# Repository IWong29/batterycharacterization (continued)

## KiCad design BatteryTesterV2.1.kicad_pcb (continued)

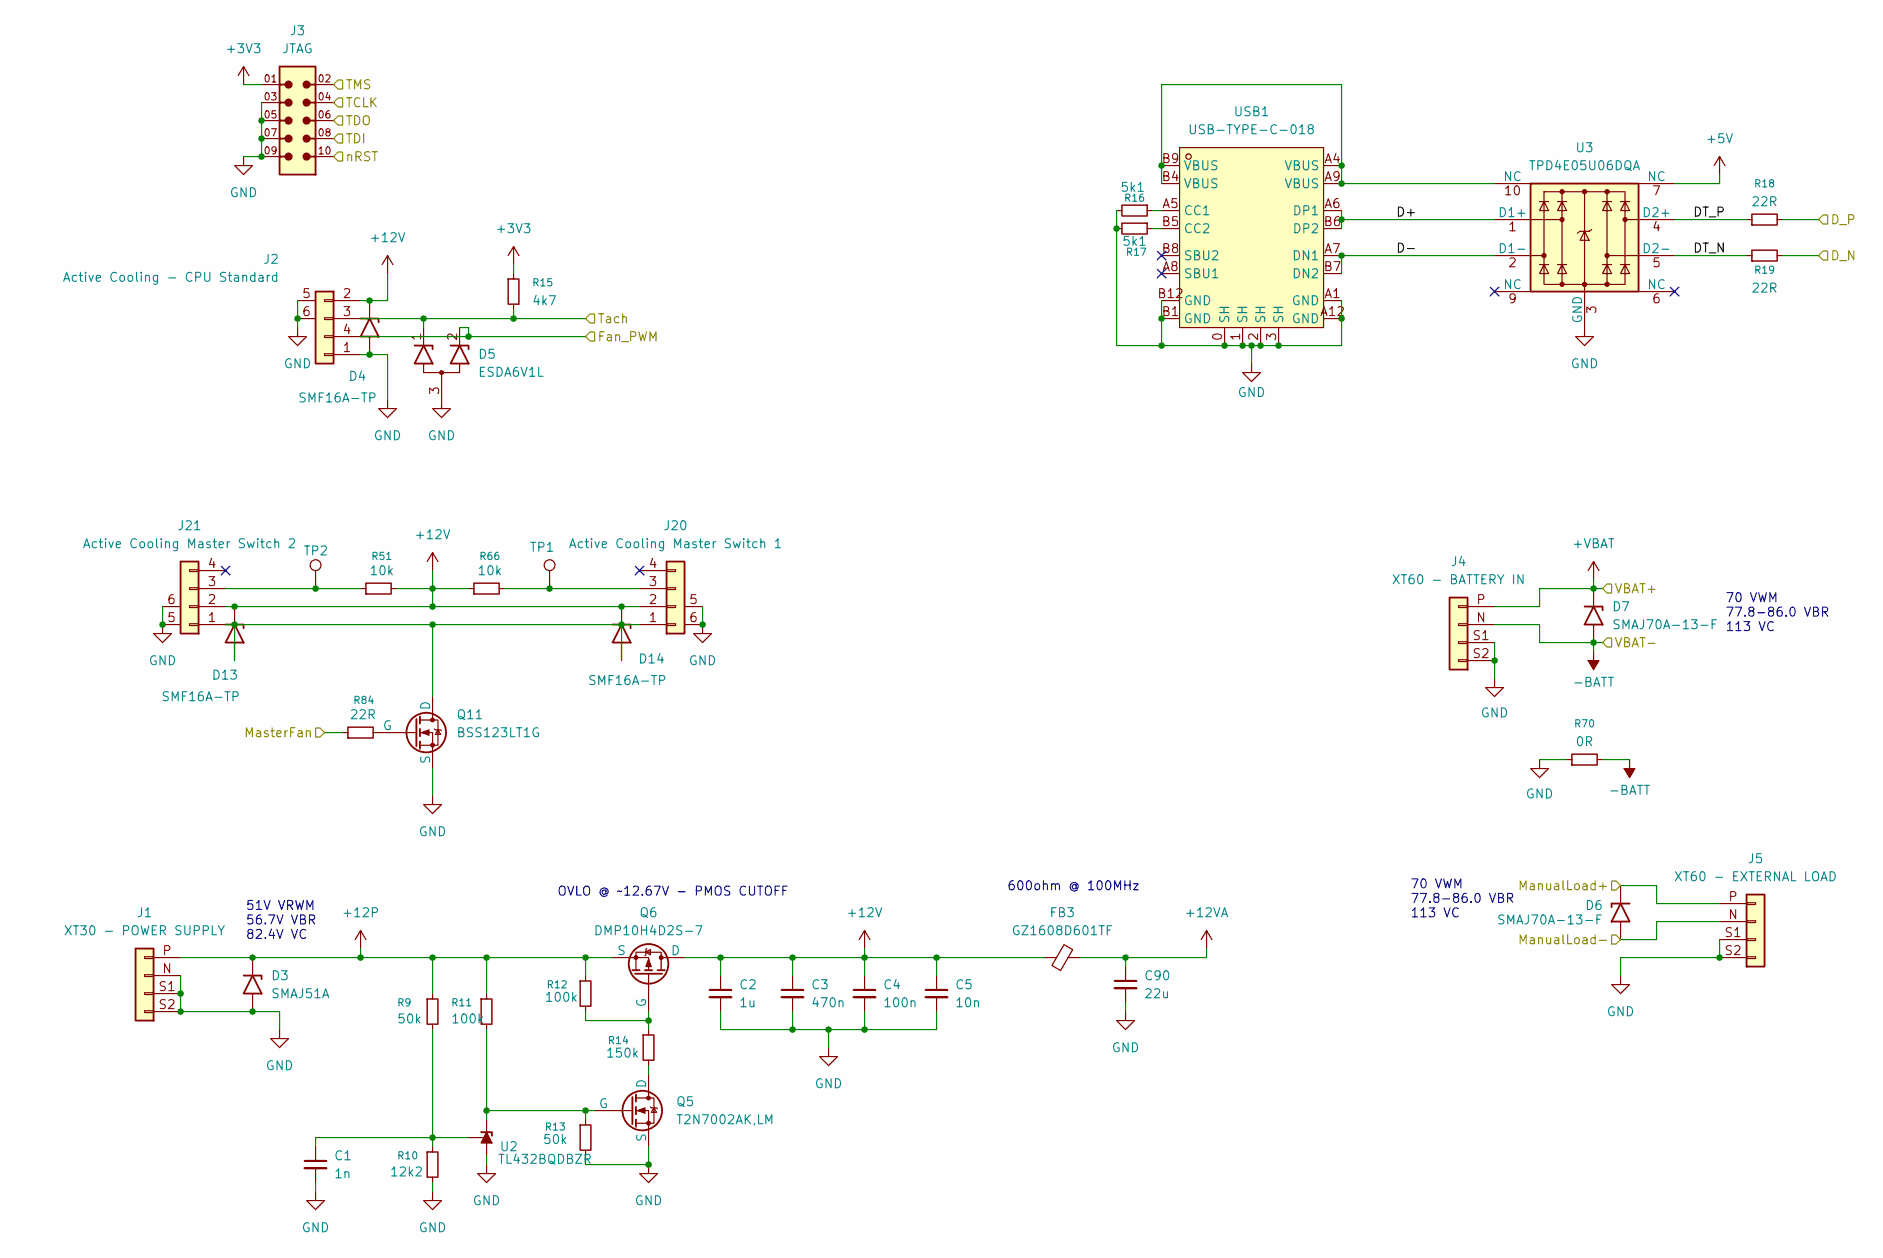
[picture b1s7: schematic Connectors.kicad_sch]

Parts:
C1: 1n; C_0603_1608Metric
C2: 1u; C_0603_1608Metric
C3: 470n; C_0603_1608Metric
C4: 100n; C_0603_1608Metric
C5: 10n; C_0603_1608Metric
C90: 22u; C_1206_3216Metric
D3: SMAJ51A; D_SMA
D4, D13, D14: SMF16A-TP; D_SMF
D5: ESDA6V1L; SOT-23
D6, D7: SMAJ70A-13-F; D_SMA
FB3: GZ1608D601TF; C_0603_1608Metric
J1: XT30 - POWER SUPPLY; AMASS_XT30PW-M
J2: Active Cooling - CPU Standard; CONN-SMD_4P-P1.00_SM04B-SRSS-TB-LF-SN
J3: JTAG; JTAG_SAMTEC_FTSH-105-01-X-DV-P-K-X
J4: XT60 - BATTERY IN; XT60
J5: XT60 - EXTERNAL LOAD; XT60
J20: Active Cooling Master Switch 1; CONN-SMD_4P-P1.00_SM04B-SRSS-TB-LF-SN
J21: Active Cooling Master Switch 2; CONN-SMD_4P-P1.00_SM04B-SRSS-TB-LF-SN
Q5: T2N7002AK,LM; SOT-23-3
Q6: DMP10H4D2S-7; SOT-23-3
Q11: BSS123LT1G; SOT-23-3
R9, R13: 50k; C_0805_2012Metric
R10: 12k2; R_0603_1608Metric
R11, R12: 100k; R_0603_1608Metric
R14: 150k; R_0603_1608Metric
R15: 4k7; R_0603_1608Metric
R16, R17: 5k1; R_0603_1608Metric
R18, R19: 22R; R_0603_1608Metric
R51, R66: 10k; C_0805_2012Metric
R70: 0R; R_0603_1608Metric
R84: 22R; C_0805_2012Metric
TP1, TP2: TestPoint; TestPoint_Pad_D1.0mm
U2: TL432BQDBZR; SOT-23-3
U3: TPD4E05U06DQA; USON-10_2.5x1.0mm_P0.5mm
USB1: USB-TYPE-C-018; USB-C_SMD-TYPE-C18; MPN USB-TYPE-C-018; LCSC Part C2927038

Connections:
+3V3: J3.01, R15.1; also elsewhere on the board
+5V: U3.7 (NC); also elsewhere on the board
+12P: D3.1 (A1), J1.P (Pin_4), Q6.3 (S), R9.1, R11.1, R12.1; also elsewhere on the board
+12V: C2.1, C3.1, C4.1, C5.1, D4.1 (A1), D13.1 (A1), D14.1 (A1), FB3.1, J2.2, J20.2, J21.2, Q6.1 (D), R51.2, R66.1; also elsewhere on the board
+12VA: C90.1, FB3.2; also elsewhere on the board
+VBAT: D7.1 (A1), J4.P (Pin_4); also elsewhere on the board
-BATT: D6.2 (A2), D7.2 (A2), J4.N (Pin_3), J5.N (Pin_3), R70.2; also elsewhere on the board
/BatteryV2/ExternalLoad+: D6.1 (A1), J5.P (Pin_4); also elsewhere on the board
/Connectors/D+: U3.1 (D1+), USB1.A6 (DP1), USB1.B6 (DP2)
/Connectors/D-: U3.2 (D1-), USB1.A7 (DN1), USB1.B7 (DN2)
/Connectors/DT_N: R19.1, U3.5 (D2-)
/Connectors/DT_P: R18.1, U3.4 (D2+)
/Connectors/D_N: R19.2; also elsewhere on the board
/Connectors/D_P: R18.2; also elsewhere on the board
/Connectors/Fan_PWM: D5.2 (K2), J2.4; also elsewhere on the board
/Connectors/MasterFan: R84.1; also elsewhere on the board
/Connectors/TCLK: J3.04; also elsewhere on the board
/Connectors/TDI: J3.08; also elsewhere on the board
/Connectors/TDO: J3.06; also elsewhere on the board
/Connectors/TMS: J3.02; also elsewhere on the board
/Connectors/Tach: D5.1 (K1), J2.3, R15.2; also elsewhere on the board
/Connectors/nRST: J3.10; also elsewhere on the board
GND: C1.2, C2.2, C3.2, C4.2, C5.2, C90.2, D3.2 (A2), D4.2 (A2), D5.3 (A), J1.N (Pin_3), J1.S1 (Pin_2), J1.S2 (Pin_1), J2.1, J2.5, J2.6, J3.03, J3.05, J3.07, J3.09, J4.S1 (Pin_2), J4.S2 (Pin_1), J5.S1 (Pin_2), J5.S2 (Pin_1), J20.5, J20.6, J21.5, J21.6, Q5.3 (S), Q11.3 (S), R10.2, R13.2, R16.2, R17.2, R70.1, U2.3 (A), U3.3 (GND), U3.8 (GND), USB1.0 (SH), USB1.1 (SH), USB1.2 (SH), USB1.3 (SH), USB1.A1 (GND), USB1.A12 (GND), USB1.B1 (GND), USB1.B12 (GND); also elsewhere on the board
unnamed: D13.2 (A2), D14.2 (A2), J20.1, J21.1, Q11.1 (D)
unnamed: J20.3, R66.2, TP1.1
unnamed: J21.3, R51.1, TP2.1
unnamed: Q5.1 (D), R14.2
unnamed: Q5.2 (G), R11.2, R13.1, U2.1 (K)
unnamed: Q6.2 (G), R12.2, R14.1
unnamed: Q11.2 (G), R84.2
unnamed: C1.1, R9.2, R10.1, U2.2 (REF)
unnamed: U3.10 (NC), USB1.A4 (VBUS), USB1.A9 (VBUS), USB1.B4 (VBUS), USB1.B9 (VBUS)
unnamed: R16.1, USB1.A5 (CC1)
unnamed: R17.1, USB1.B5 (CC2)

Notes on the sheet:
70 VWM 77.8-86.0 VBR 113 VC
600ohm @ 100MHz
51V VRWM 56.7V VBR 82.4V VC
OVLO @ ~12.67V - PMOS CUTOFF

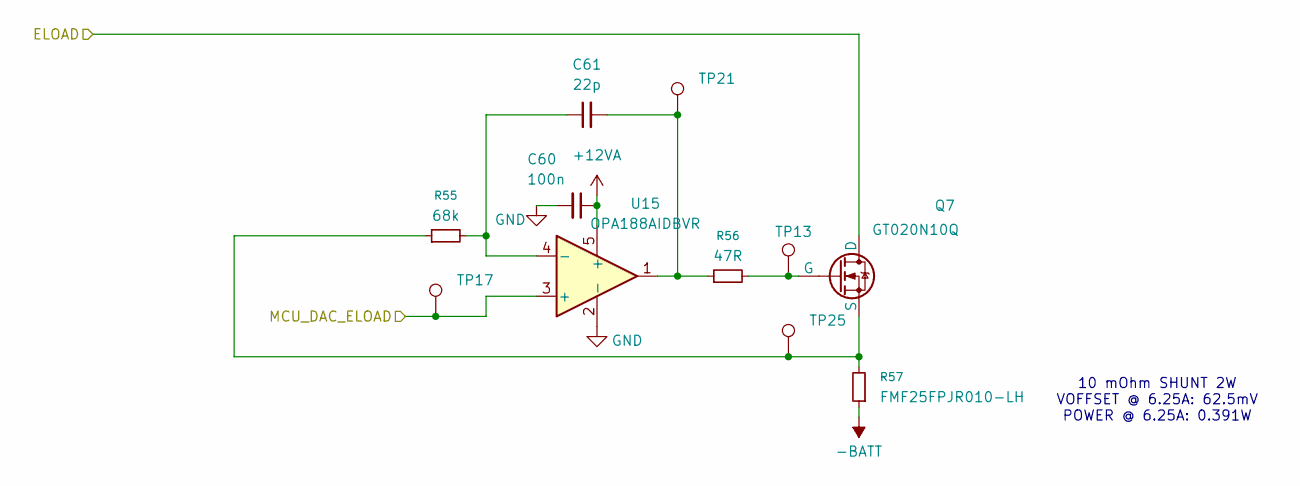
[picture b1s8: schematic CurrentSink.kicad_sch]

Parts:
C60: 100n; C_0603_1608Metric
C61: 22p; C_0603_1608Metric
Q7: GT020N10Q; TO-247-3_Horizontal_TabUp
R55: 68k; R_0603_1608Metric
R56: 47R; R_0603_1608Metric
R57: FMF25FPJR010-LH; R_2512_6332Metric
TP13, TP17, TP21, TP25: TestPoint; TestPoint_Pad_D1.0mm
U15: OPA188AIDBVR; SOT-23-5

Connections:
+12VA: C60.1, U15.5 (+); also elsewhere on the board
-BATT: R57.1; also elsewhere on the board
/BatteryV2/ELOAD: Q7.1 (D); also elsewhere on the board
/ELOAD/CurrentSink/MCU_DAC_ELOAD: TP17.1, U15.3 (+); also elsewhere on the board
GND: C60.2, U15.2 (-); also elsewhere on the board
unnamed: C61.1, R55.2, U15.4 (-)
unnamed: C61.2, R56.1, TP21.1, U15.1
unnamed: Q7.2 (G), R56.2, TP13.1
unnamed: Q7.3 (S), R55.1, R57.2, TP25.1

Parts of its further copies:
C63, C66, C69: 100n; C_0603_1608Metric
C64, C67, C70: 22p; C_0603_1608Metric
Q8, Q9, Q10: GT020N10Q; TO-247-3_Horizontal_TabUp
R59, R63, R67: 68k; R_0603_1608Metric
R60, R64, R68: 47R; R_0603_1608Metric
R61, R65, R69: FMF25FPJR010-LH; R_2512_6332Metric
TP14, TP15, TP16, TP18, TP19, TP20, TP22, TP23, TP24, TP26, TP27, TP28: TestPoint; TestPoint_Pad_D1.0mm
U16, U17, U18: OPA188AIDBVR; SOT-23-5

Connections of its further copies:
+12VA: C63.1, C66.1, C69.1, U16.5 (+), U17.5 (+), U18.5 (+); also elsewhere on the board
-BATT: R61.1, R65.1, R69.1; also elsewhere on the board
/BatteryV2/ELOAD: Q8.1 (D), Q9.1 (D), Q10.1 (D); also elsewhere on the board
/ELOAD/CurrentSink/MCU_DAC_ELOAD: TP18.1, TP19.1, TP20.1, U16.3 (+), U17.3 (+), U18.3 (+); also elsewhere on the board
GND: C63.2, C66.2, C69.2, U16.2 (-), U17.2 (-), U18.2 (-); also elsewhere on the board
unnamed: C64.1, R59.2, U16.4 (-)
unnamed: C64.2, R60.1, TP22.1, U16.1
unnamed: C67.1, R63.2, U17.4 (-)
unnamed: C67.2, R64.1, TP23.1, U17.1
unnamed: C70.1, R67.2, U18.4 (-)
unnamed: C70.2, R68.1, TP24.1, U18.1
unnamed: Q8.2 (G), R60.2, TP14.1
unnamed: Q8.3 (S), R59.1, R61.2, TP26.1
unnamed: Q9.2 (G), R64.2, TP15.1
unnamed: Q9.3 (S), R63.1, R65.2, TP27.1
unnamed: Q10.2 (G), R68.2, TP16.1
unnamed: Q10.3 (S), R67.1, R69.2, TP28.1

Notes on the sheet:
10 mOhm SHUNT 2W VOFFSET @ 6.25A: 62.5mV POWER @ 6.25A: 0.391W

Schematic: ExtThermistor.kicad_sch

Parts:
C72: 100n; C_0603_1608Metric
J7: Thermistor; JST_SH_SM02B-SRSS-TB_1x02-1MP_P1.00mm_Horizontal
R71: 10k 1% Thin Film; R_0603_1608Metric

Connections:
+A3V3: R71.1; also elsewhere on the board
/Temperature/ExtThermistor/Thermistor: C72.1, J7.2, R71.2; also elsewhere on the board
GND: C72.2, J7.1, J7.MP; also elsewhere on the board

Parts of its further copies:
C73, C74, C75, C76, C77, C78, C79, C82, C83, C84, C85: 100n; C_0603_1608Metric
J8, J9, J10, J11, J12, J13, J14, J15, J16, J17, J18: Thermistor; JST_SH_SM02B-SRSS-TB_1x02-1MP_P1.00mm_Horizontal
R72, R73, R74, R75, R76, R77, R78, R79, R80, R81, R82: 10k 1% Thin Film; R_0603_1608Metric

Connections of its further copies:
+A3V3: R72.1, R73.1, R74.1, R75.1, R76.1, R77.1, R78.1, R79.1, R80.1, R81.1, R82.1; also elsewhere on the board
/Temperature/ExtThermistor1/Thermistor: C73.1, J8.2, R72.2; also elsewhere on the board
/Temperature/ExtThermistor2/Thermistor: C74.1, J9.2, R73.2; also elsewhere on the board
/Temperature/ExtThermistor3/Thermistor: C75.1, J10.2, R74.2; also elsewhere on the board
/Temperature/ExtThermistor4/Thermistor: C76.1, J11.2, R75.2; also elsewhere on the board
/Temperature/ExtThermistor5/Thermistor: C77.1, J12.2, R76.2; also elsewhere on the board
/Temperature/ExtThermistor6/Thermistor: C78.1, J13.2, R77.2; also elsewhere on the board
/Temperature/ExtThermistor7/Thermistor: C79.1, J14.2, R78.2; also elsewhere on the board
/Temperature/ExtThermistor8/Thermistor: C82.1, J15.2, R79.2; also elsewhere on the board
/Temperature/ExtThermistor9/Thermistor: C83.1, J16.2, R80.2; also elsewhere on the board
/Temperature/ExtThermistor10/Thermistor: C84.1, J17.2, R81.2; also elsewhere on the board
/Temperature/ExtThermistor11/Thermistor: C85.1, J18.2, R82.2; also elsewhere on the board
GND: C73.2, C74.2, C75.2, C76.2, C77.2, C78.2, C79.2, C82.2, C83.2, C84.2, C85.2, J8.1, J8.MP, J9.1, J9.MP, J10.1, J10.MP, J11.1, J11.MP, J12.1, J12.MP, J13.1, J13.MP, J14.1, J14.MP, J15.1, J15.MP, J16.1, J16.MP, J17.1, J17.MP, J18.1, J18.MP; also elsewhere on the board

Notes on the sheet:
B25/5 = 3950K 10k @ 25C -30C to 105C Vout: 1.65V @ 25C, 0.66V @ 60C
MF52D 103F3950

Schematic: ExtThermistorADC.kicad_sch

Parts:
C80: 100n; C_0603_1608Metric
U19: TLA2024IRUGR; IC_TLA2024IRUGR; PARTREV November 2017

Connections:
+A3V3: C80.1, U19.1 (ADDR), U19.8 (VDD); also elsewhere on the board
/MCU/SCL1: U19.10 (SCL); also elsewhere on the board
/MCU/SDA1: U19.9 (SDA); also elsewhere on the board
/Temperature/ExtThermistor1/Thermistor: U19.5 (AIN1); also elsewhere on the board
/Temperature/ExtThermistor2/Thermistor: U19.6 (AIN2); also elsewhere on the board
/Temperature/ExtThermistor7/Thermistor: U19.7 (AIN3); also elsewhere on the board
/Temperature/ExtThermistor/Thermistor: U19.4 (AIN0); also elsewhere on the board
GND: C80.2, U19.3 (GND); also elsewhere on the board

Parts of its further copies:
C81, C86: 100n; C_0603_1608Metric
U20, U21: TLA2024IRUGR; IC_TLA2024IRUGR; PARTREV November 2017

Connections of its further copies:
+A3V3: C81.1, C86.1, U20.8 (VDD), U21.8 (VDD); also elsewhere on the board
/MCU/SCL1: U20.10 (SCL), U21.1 (ADDR), U21.10 (SCL); also elsewhere on the board
/MCU/SDA1: U20.9 (SDA), U21.9 (SDA); also elsewhere on the board
/Temperature/ExtThermistor3/Thermistor: U20.4 (AIN0); also elsewhere on the board
/Temperature/ExtThermistor4/Thermistor: U20.6 (AIN2); also elsewhere on the board
/Temperature/ExtThermistor5/Thermistor: U20.7 (AIN3); also elsewhere on the board
/Temperature/ExtThermistor6/Thermistor: U20.5 (AIN1); also elsewhere on the board
/Temperature/ExtThermistor8/Thermistor: U21.4 (AIN0); also elsewhere on the board
/Temperature/ExtThermistor9/Thermistor: U21.6 (AIN2); also elsewhere on the board
/Temperature/ExtThermistor10/Thermistor: U21.7 (AIN3); also elsewhere on the board
/Temperature/ExtThermistor11/Thermistor: U21.5 (AIN1); also elsewhere on the board
GND: C81.2, C86.2, U20.1 (ADDR), U20.3 (GND), U21.3 (GND); also elsewhere on the board

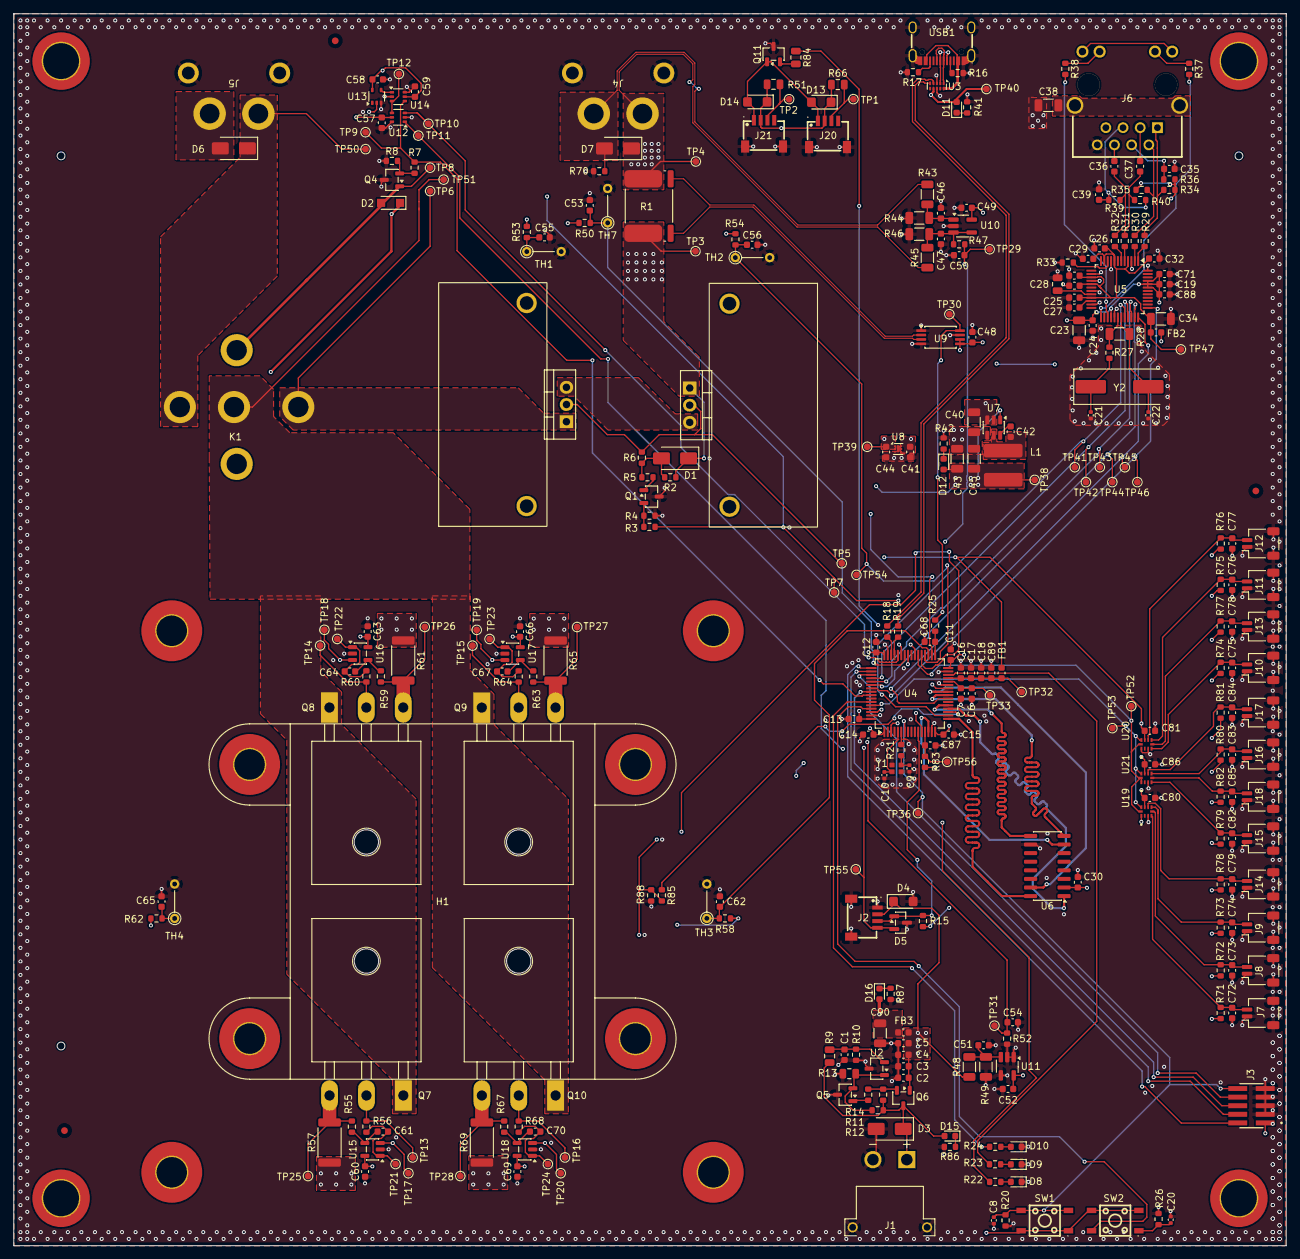
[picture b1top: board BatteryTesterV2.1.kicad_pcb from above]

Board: 4 copper layers, 188.0 x 182.0 mm, 312 parts (0 on the bottom side), 153 nets.

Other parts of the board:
C57, C58, C59: 100n; C_0603_1608Metric
D1: 3SMAJ5931B-TP; D_SMA
D2: B0540W-7-F; Nexperia_CFP3_SOD-123W
H1: Spread_MountingHole; Spreader_Mount
K1: A31CSP12VDC2
Q1, Q4: BSS123LT1G; SOT-23-3
Q2, Q3: GT250P10T; TO-220 w heatsink
R1: HOVB4026-5W-2mR-1%; R_Shunt_Isabellenhuette_BVR4026
R2, R4, R8: 100k; R_0603_1608Metric
R3, R7: 100R; R_0603_1608Metric
R5: 1k; R_0603_1608Metric
R6: 47R; R_0603_1608Metric
TP3, TP4, TP5, TP6, TP7, TP8, TP9, TP10, TP11, TP12, TP50, TP51: TestPoint; TestPoint_Pad_D1.0mm
U12, U14: 74LVC1G373; SOT-363_SC-70-6
U13: 74AHC1G04; SOT-353_SC-70-5

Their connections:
+3V3: C57.1, C58.1, C59.1, U12.5 (VCC), U13.5 (VCC), U14.5 (VCC); also elsewhere on the board
+12V: D2.1 (K), K1.2; also elsewhere on the board
+VBAT: R1.4, TP4.1; also elsewhere on the board
/BatteryV2/ELOAD: K1.4, TP51.1; also elsewhere on the board
/BatteryV2/ExternalLoad+: K1.5, TP50.1; also elsewhere on the board
/BatteryV2/FetDrain: D1.1 (K), Q2.1 (D), R1.1, R2.1, TP3.1
/BatteryV2/FetRelay: K1.3, Q3.1 (D), TP6.1
/BatteryV2/FetSource: Q2.3 (S), Q3.3 (S)
/BatteryV2/MasterGate: R3.1, TP7.1, U13.2; also elsewhere on the board
/BatteryV2/RelayCloseOut: R7.1, TP9.1, U14.4 (Q); also elsewhere on the board
/BatteryV2/RelayClose_Latch: TP11.1, U12.1 (LE); also elsewhere on the board
/BatteryV2/RelayClose_MCU: TP10.1, U12.3 (D); also elsewhere on the board
/BatteryV2/SysCurrent+: R1.3; also elsewhere on the board
/BatteryV2/SysCurrent-: R1.2; also elsewhere on the board
GND: C57.2, C58.2, C59.2, Q1.3 (S), Q4.3 (S), R4.1, R8.1, U12.2 (GND), U12.6 (~OE), U13.3 (GND), U14.2 (GND), U14.6 (~OE); also elsewhere on the board
unnamed: D1.2 (A), R2.2, R5.1, R6.1
unnamed: D2.2 (A), K1.1, Q4.1 (D), TP8.1
unnamed: Q1.1 (D), R5.2
unnamed: Q1.2 (G), R3.2, R4.2
unnamed: Q2.2 (G), Q3.2 (G), R6.2, TP5.1
unnamed: Q4.2 (G), R7.2, R8.2
unnamed: U13.4, U14.1 (LE)
RelayClose_SR1: TP12.1, U12.4 (Q), U14.3 (D)
